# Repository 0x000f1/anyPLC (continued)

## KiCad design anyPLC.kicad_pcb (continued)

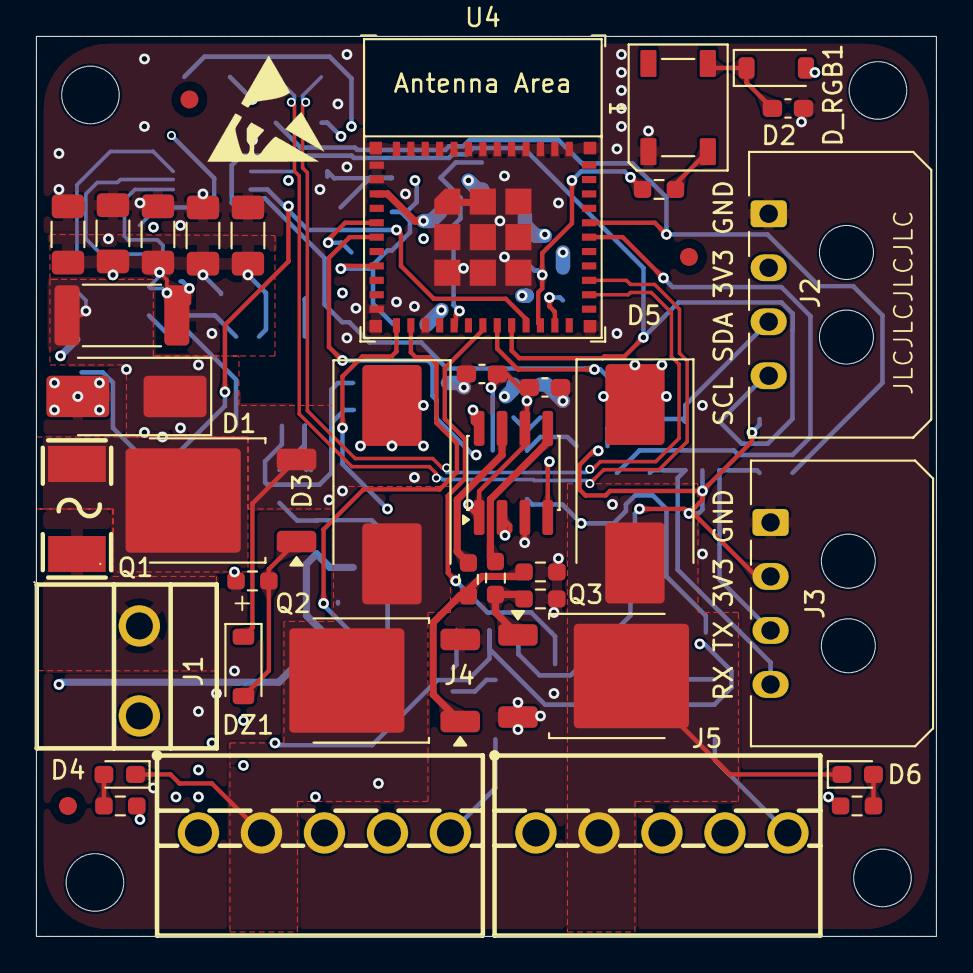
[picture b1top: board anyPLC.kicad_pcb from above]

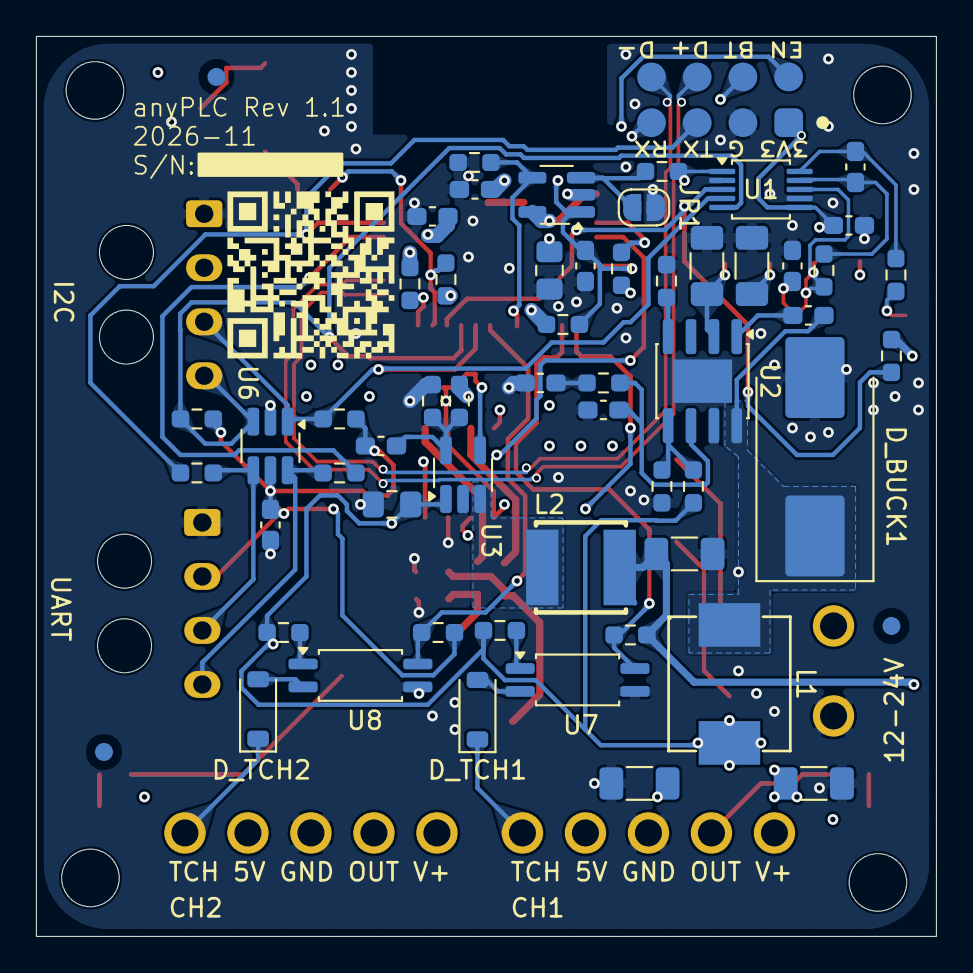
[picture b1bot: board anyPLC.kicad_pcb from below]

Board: 4 copper layers, 50.0 x 50.0 mm, 102 parts (59 on the bottom side), 53 nets.

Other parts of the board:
QR1: GitHub_QR_AnyPLC

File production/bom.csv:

Designator,Footprint,Quantity,Value,LCSC Part #
"C1, C25, C27, C28, C5, C5_B1",1206,6,10µF 50V X7R,
C10,1206,1,22uF 16V,
"C11, C13, C14, C20, C26, C3, C4, C6",0603,8,100nF 50V X7R,
"C11_B1, C9",0805,2,10uF 25V,
C12,0603,1,1uF 50V X7R,
C2,1206,1,10uF 50V X7R,
C29,0603,1,100pF C0G 0603,
"C7, C8",1206,2,22uF 16V X7R,
C_CMP1,0603,1,4.7nF,
C_CMP2,0603,1,100pF,
C_DRV1,0603,1,1uF 50V,
C_DRV2,0603,1,100nF 50V,
D1,D_SMB_Handsoldering,1,SMBJ26A,
D2,LED_WS2812B_PLCC4_5.0x5.0mm_P3.2mm,1,WS2812B,
"D3, D5",D_SMC_Handsoldering,2,B560C,
"D4, D6",0603,2,LED_Small,
DZ1,D_SOD-123,1,BZT52C15,
D_BUCK1,D_SMC_Handsoldering,1,B560C 60V 5A,
"D_RGB1, D_TCH1, D_TCH2",D_SOD-123,3,1N4148W,
F1,F2410,1,JFC2410-1800TS,
J1,CONN-TH_KF250NH-5.0-2P,1,KF250NH-5.0-2P,
"J2, J3",Molex_Micro-Fit_3.0_43650-0400_1x04_P3.00mm_Horizontal,2,43650-0400,
"J4, J5",CONN-TH_KF250NH-3.5-5P,2,KF250NH-3.5-5P,
J6,TestPoint_2x04_P2.54mm_D1.6mm_SMD,1,Conn_01x08,
L1,IND-SMD_L7.3-W6.6,1,10µH 5.5A,
L2,IND-SMD_L5.0-W5.0_FNR50XXS,1,4.7µH 3.8A,
Q1,TO-252-2,1,MCU80P06Y-TP,
"Q2, Q3",TO-252-2,2,IPD079N06L3G-TP,
R1,2512,1,10m 3W 1%,
"R10, R9, R_WD_EN1",0603,3,4.7k,
"R11, R12",0603,2,100R,
"R13, R18, R3, R4",0603,4,10R,
"R14, R15, R19, R20, R26, R5, R6, R7, R_INA1",0603,9,10k,
"R16, R21",0603,2,2.2k,
"R17, R2, R22",0603,3,22k,
R8,0603,1,330R,
"R_CMP1, R_FB2",0603,2,10kΩ 1%,
R_FB1,0603,1,52.3kΩ 1%,
R_FB3,0603,1,100kΩ 1%,
R_FB4,0603,1,22kΩ 1%,
R_RT1,0603,1,200kΩ 1%,
R_WDI1,0603,1,100k,
U1,TSSOP-10_3x3mm_P0.5mm,1,INA226AIDGSR,
U2,SOIC-8-1EP_3.9x4.9mm_P1.27mm_EP2.41x3.3mm,1,TPS54360DDA,
U3,SOT-23-5_HandSoldering,1,SY8089AAAC,
U4,ESP32-C3-MINI-1,1,ESP32-C3-MINI-1-H4,
U5,SOT-23-5_HandSoldering,1,STWD100NYWY3F,STWD100NYWY3F
U6,SOT-23-6_Handsoldering,1,SRV05-4,
"U7, U8",SOP-4_4.4x2.6mm_P1.27mm,2,TLP293,
U_DRV1,SOIC-8_3.9x4.9mm_P1.27mm,1,UCC27524ADR,
